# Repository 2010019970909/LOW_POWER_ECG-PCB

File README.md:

---
## Version française ci-dessous
---
# PCB-ECG-Basse-consommation
Chaîne d'instrumentation basse consomation destinée à une application de capture ECG. En plus du projet KiCad, vous trouverez les codes utilisées pour échantillonner, afficher et enregistrer les données, à l'aide d'un carte Arduino Uno.

# À propos du projet
Ce projet utilise la récolte d'énergie pour réaliser un électrocardiographe (ECG). Donc, la chaîne d'instrumentation a besoin d'être basse consommation. Le schéma du circuit est inspiré de la datasheet de l'"INA321". Il s'agit d'un composant de Texas Instruments.

# À propos de nous
Nous sommes trois étudiants de la Faculté Polytechnique de Mons (Université de Mons, UMons). Antoine DUFRANE, Charlotte LUYPAERT et Vincent STRAGIER (moi-même) avons travaillé sur ce projet. C'est un projet que nous faisons dans le cadre de notre troisième année dans la Faculté Polytechnique, option electricité.

---
## English version below
---
# LOW_POWER_ECG-PCB
Low power channel of instrumentation for an ECG application. In complement of the KiCad project you will find codes used to sample, show and to record data with the help of an Arduino Uno card.

# About it
This project is using powerharvesting to make an electrocardiograph (ECG). So the channel of instrumentation needs to be low power. The circuit schematic is inspired from the "INA321" datasheet. It's a Texas Instruments component.

# About us
We are 3 students of the Polytechnic Faculty of Mons (University of Mons in Belgium, UMons). Antoine DUFRANE, Charlotte LUYPAERT and Vincent STRAGIER (myself) have been working on this project. It's a project for our third year in the Electrical Engineering Faculty

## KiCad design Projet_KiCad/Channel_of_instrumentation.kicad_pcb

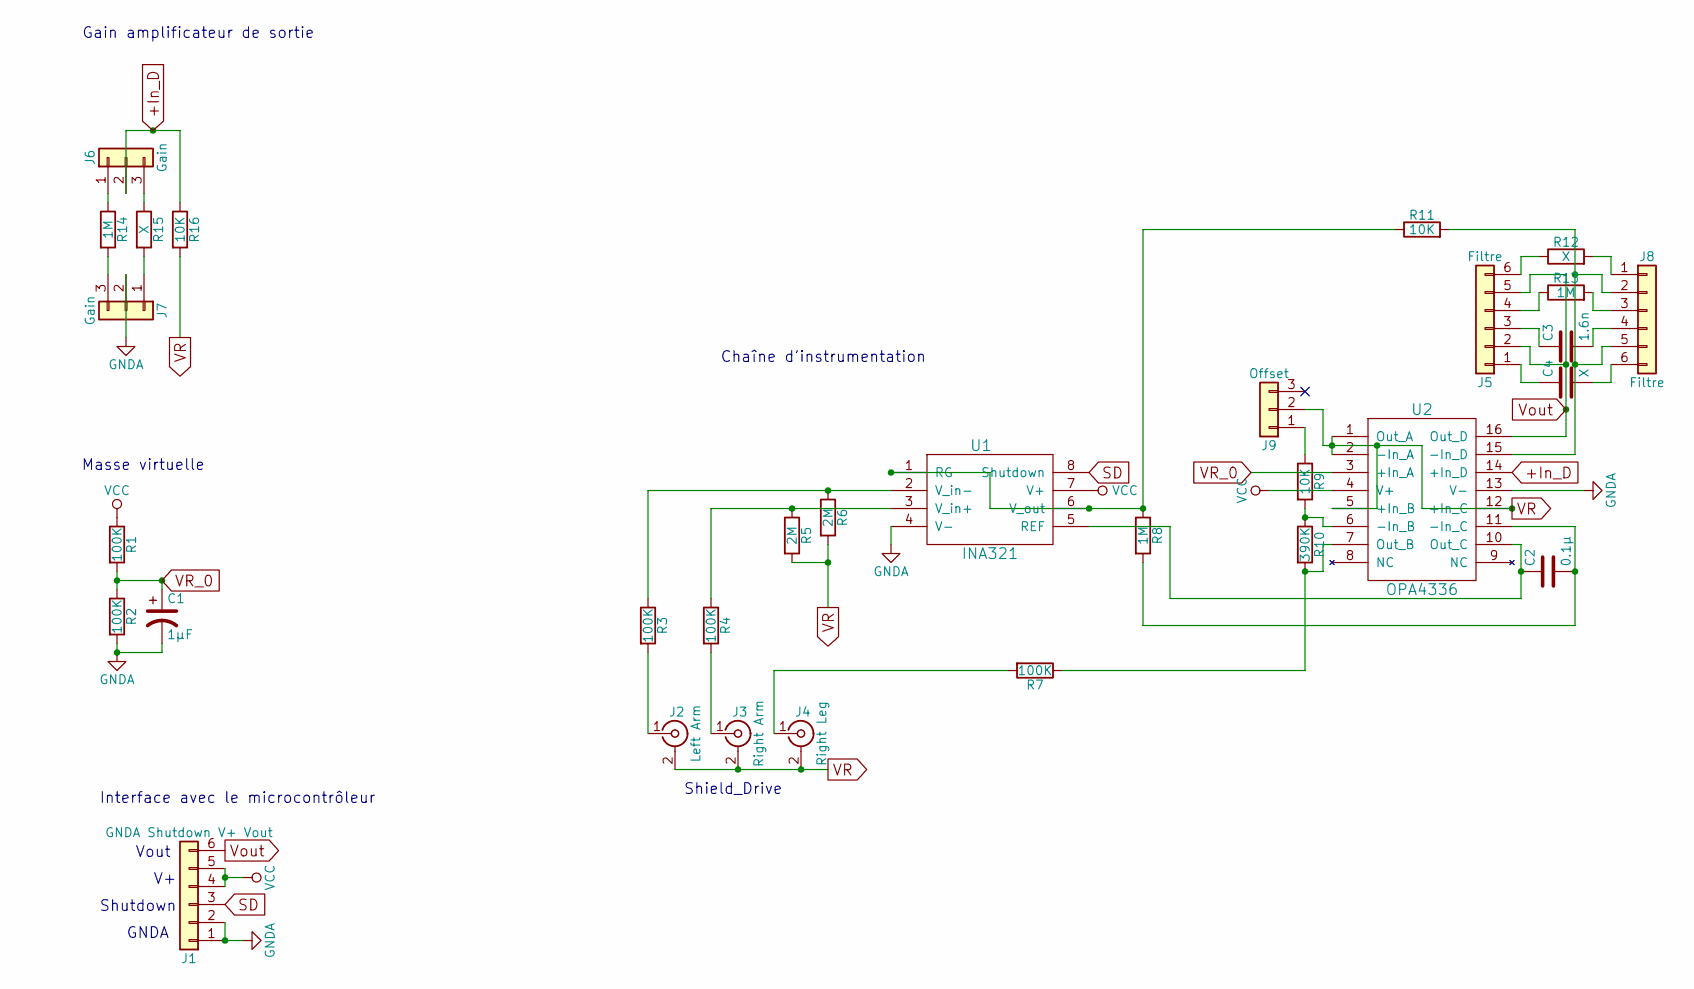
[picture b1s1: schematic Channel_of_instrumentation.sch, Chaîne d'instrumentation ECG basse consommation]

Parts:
C1: 1µF; CP_Radial_D6.3mm_P2.50mm
C2: 0.1µ; C_Disc_D7.5mm_W4.4mm_P5.00mm
C3: 1.6n; C_Disc_D7.5mm_W4.4mm_P5.00mm
C4: X; C_Disc_D7.5mm_W4.4mm_P5.00mm
J1: GNDA Shutdown V+ Vout; Pin_Header_Straight_1x06_Pitch2.54mm
J2: Left Arm; JEITA_RC-5231
J3: Right Arm; JEITA_RC-5231
J4: Right Leg; JEITA_RC-5231
J5, J8: Filtre; Pin_Header_Straight_1x06_Pitch2.54mm
J6, J7: Gain; Pin_Header_Straight_1x03_Pitch2.54mm
J9: Offset; Pin_Header_Straight_1x03_Pitch2.54mm
R1, R2, R3, R4, R7: 100K; R_Axial_DIN0207_L6.3mm_D2.5mm_P10.16mm_Horizontal
R5, R6: 2M; R_Axial_DIN0207_L6.3mm_D2.5mm_P10.16mm_Horizontal
R8, R13, R14: 1M; R_Axial_DIN0207_L6.3mm_D2.5mm_P10.16mm_Horizontal
R9, R11, R16: 10K; R_Axial_DIN0207_L6.3mm_D2.5mm_P10.16mm_Horizontal
R10: 390K; R_Axial_DIN0207_L6.3mm_D2.5mm_P10.16mm_Horizontal
R12, R15: X; R_Axial_DIN0207_L6.3mm_D2.5mm_P10.16mm_Horizontal
U1: INA321; MSOP-8_3x3mm_Pitch0.65mm
U2: OPA4336; DBQ0016A

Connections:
+In_D: J6.2, R16.1, U2.14 (+In_D)
GNDA: C1.2, J1.1, J1.2, J7.2, R2.2, U1.4 (V-), U2.13 (V-)
unnamed: C2.1, U1.5 (REF), U2.10 (Out_C)
unnamed: C2.2, R8.2, U2.11 (-In_C)
unnamed: C3.1, J5.3
unnamed: C3.2, J8.4
unnamed: C4.1, J5.1
unnamed: C4.2, J8.6
unnamed: J2.1 (In), R3.2
unnamed: J3.1 (In), R4.2
unnamed: J4.1 (In), R7.2
unnamed: J5.4, R13.1
unnamed: J5.6, R12.1
unnamed: J6.1, R14.1
unnamed: J6.3, R15.1
unnamed: J7.1, R15.2
unnamed: J7.3, R14.2
unnamed: J8.1, R12.2
unnamed: J8.2, J8.5, R11.2, U2.15 (-In_D)
unnamed: J8.3, R13.2
unnamed: J9.1, R9.1
unnamed: R3.1, R6.1, U1.2 (V_in-)
unnamed: R4.1, R5.1, U1.3 (V_in+)
unnamed: R9.2, R10.1, U2.6 (-In_B)
unnamed: R7.1, R10.2, U2.7 (Out_B)
unnamed: R8.1, R11.1, U1.1 (RG), U1.6 (V_out)
SD: J1.3, U1.8 (Shutdown)
VCC: J1.4, J1.5, R1.1, U1.7 (V+), U2.4 (V+)
VR: J2.2 (Ext), J3.2 (Ext), J4.2 (Ext), J9.2, R5.2, R6.2, R16.2, U2.1 (Out_A), U2.2 (-In_A), U2.5 (+In_B), U2.12 (+In_C)
VR_0: C1.1, R1.2, R2.1, U2.3 (+In_A)
Vout: J1.6, J5.2, J5.5, U2.16 (Out_D)

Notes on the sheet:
Shield_Drive
GNDA
Shutdown
Vout
Masse virtuelle
Interface avec le microcontrôleur
Gain amplificateur de sortie
Chaîne d'instrumentation

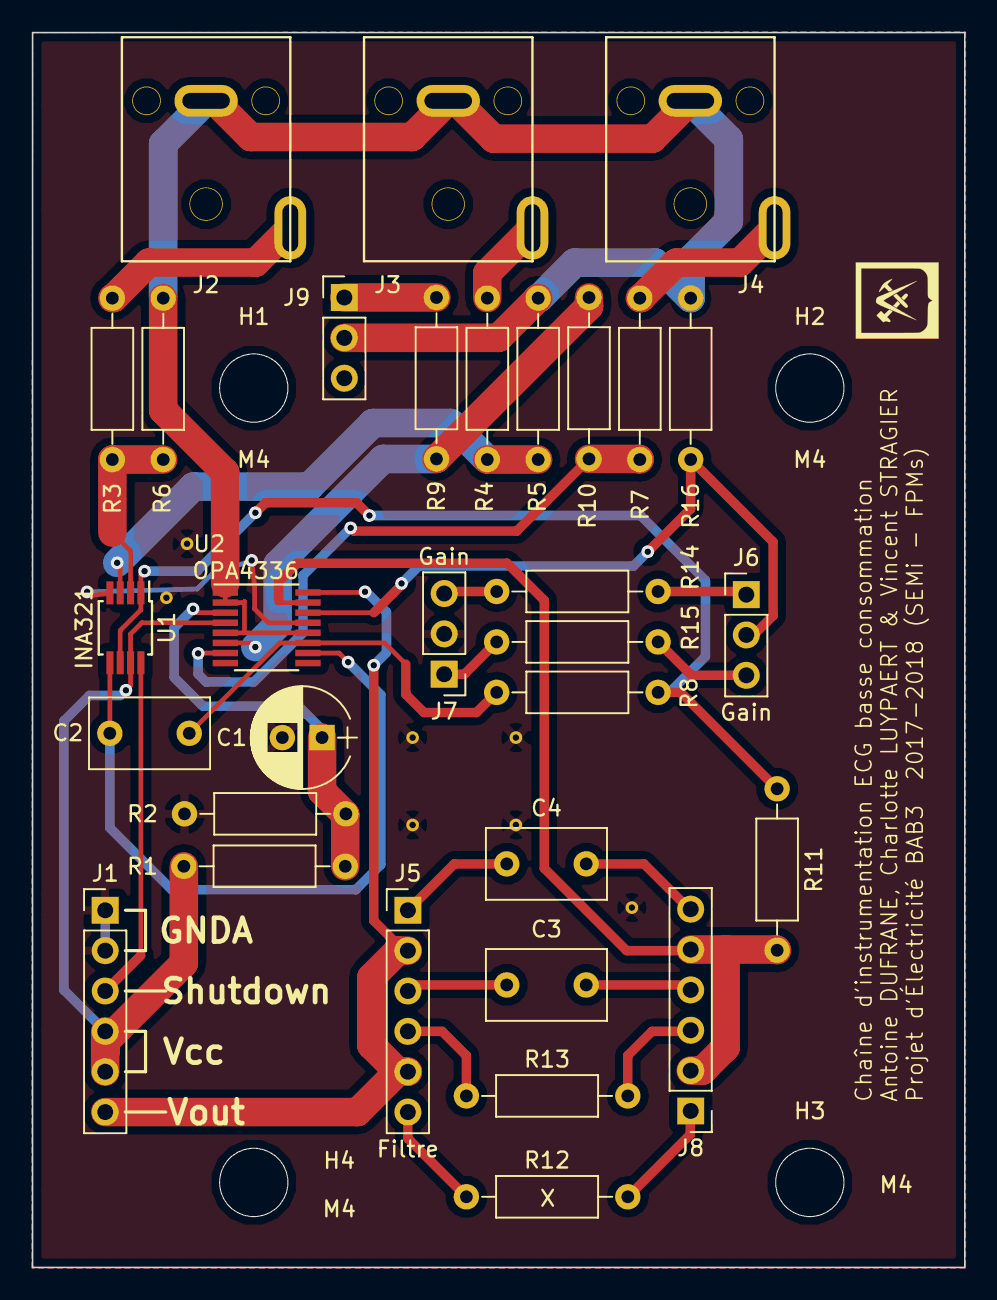
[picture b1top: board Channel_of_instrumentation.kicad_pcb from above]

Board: 2 copper layers, 58.7 x 77.7 mm, 35 parts (0 on the bottom side), 31 nets.

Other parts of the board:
H1, H2, H3, H4: M4; MountingHole_4.3mm_M4_ISO14580
